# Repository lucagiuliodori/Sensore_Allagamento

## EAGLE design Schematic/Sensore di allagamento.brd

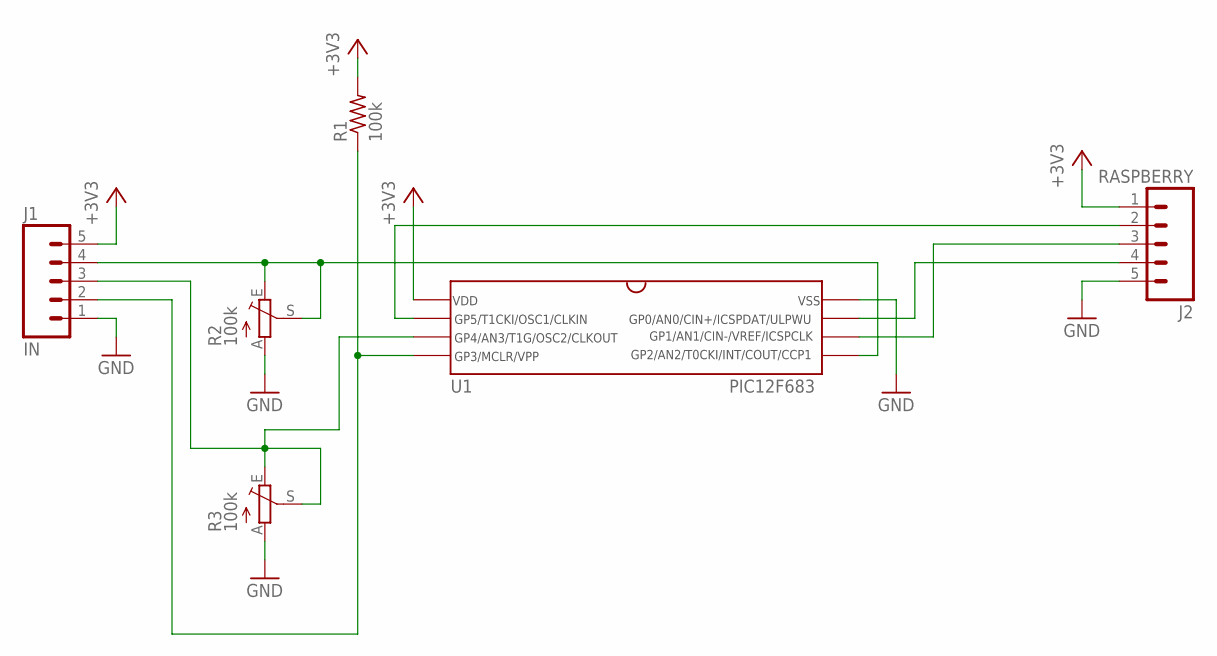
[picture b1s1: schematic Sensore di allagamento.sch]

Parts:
J1: IN; JST-5-PTH-VERT
J2: RASPBERRY; 1X05
R1: 100k; 0207/15
R2, R3: 100k; CA9V
U1: PIC12F683_RPDIP; RPDIP-8PIN

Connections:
+3V3: J1.5, J2.1, R1.2, U1.P$1
GND: J1.1, J2.5, R2.A, R3.A, U1.P$8
unnamed: J1.4, R2.E, R2.S, U1.P$5
unnamed: J2.4, U1.P$7
unnamed: J2.2, U1.P$2
unnamed: J2.3, U1.P$6
unnamed: J1.2, R1.1, U1.P$4
unnamed: J1.3, R3.E, R3.S, U1.P$3

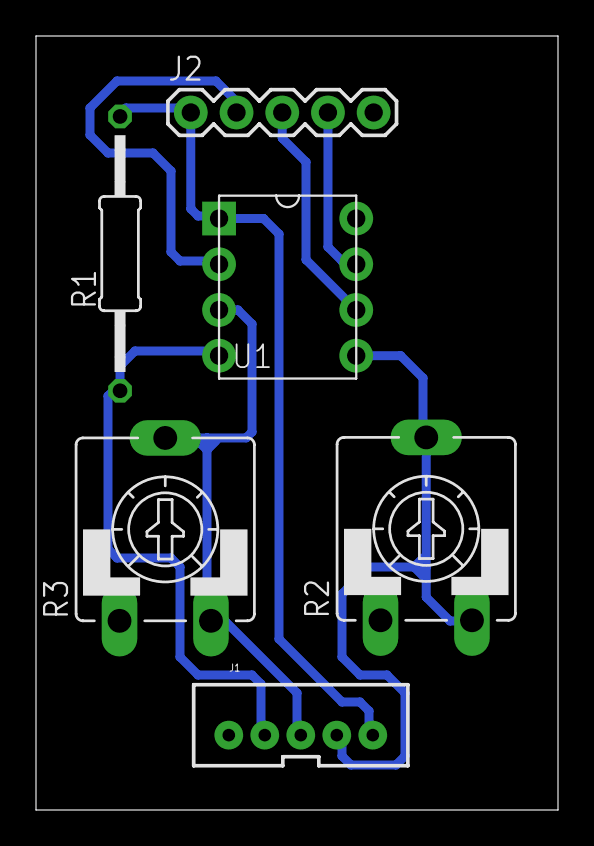
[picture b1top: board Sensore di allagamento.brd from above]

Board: 2 copper layers, 29.0 x 43.0 mm, 6 parts (0 on the bottom side), 8 nets.

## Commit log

2017-08-17 Initial adding files

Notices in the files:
parts and their libraries:
SparkFun-Connectors: Licensing: Creative Commons ShareAlike 4.0 International - https://creativecommons.org/licenses/by-sa/4.0
